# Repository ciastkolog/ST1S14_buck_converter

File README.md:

# ST1S14_buck_converter
ST1S14 buck converter board and documentation

Simple small step-down converter ST1S14:

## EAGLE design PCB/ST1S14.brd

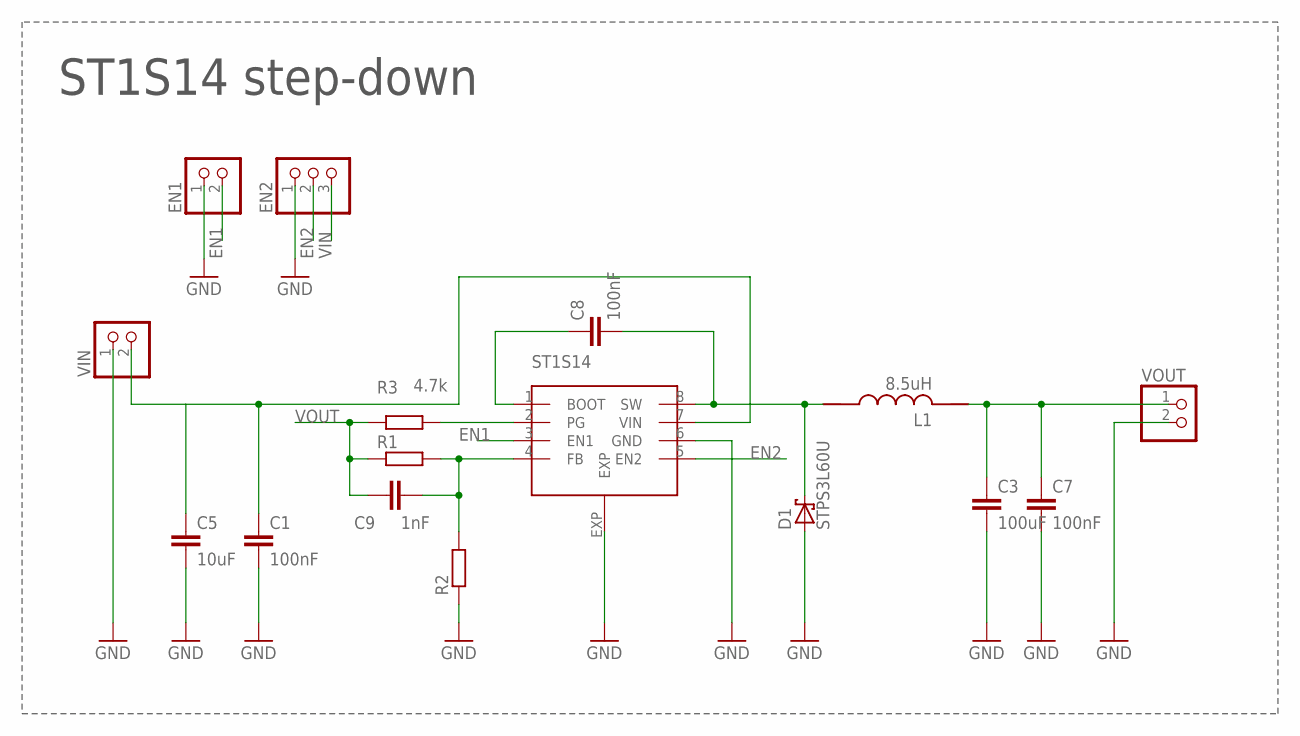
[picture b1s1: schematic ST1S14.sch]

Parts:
C1: 100nF; C1210K
C3: 100uF; C1210K
C5: 10uF; C0603
C7, C8: 100nF; C0603
C9: 1nF; C0603
D1: STPS3L60U; SMB
EN1: PINHD-1X2; 1X02
EN2: PINHD-1X3; 1X03
L1: 8.5uH; COIL1
R1, R2: R-EU_R0603; R0603
R3: 4.7k; R0603
U$1: ST1S14; HSOP8
VIN: PINHD-1X2; 1X02
VOUT: PINHD-1X2; 1X02

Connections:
EN1: EN1.2, U$1.3 (EN1)
EN2: EN2.2, U$1.5 (EN2)
GND: C1.2, C3.2, C5.2, C7.2, D1.A, EN1.1, EN2.1, R2.1, U$1.6 (GND), U$1.EXP, VIN.1, VOUT.2
unnamed: C8.1, U$1.1 (BOOT)
unnamed: C9.2, R1.2, R2.2, U$1.4 (FB)
unnamed: C8.2, D1.C, L1.1, U$1.8 (SW)
unnamed: R3.2, U$1.2 (PG)
VIN: C1.1, C5.1, EN2.3, U$1.7 (VIN), VIN.2
VOUT: C3.1, C7.1, C9.1, L1.2, R1.1, R3.1, VOUT.1

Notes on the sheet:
ST1S14 step-down

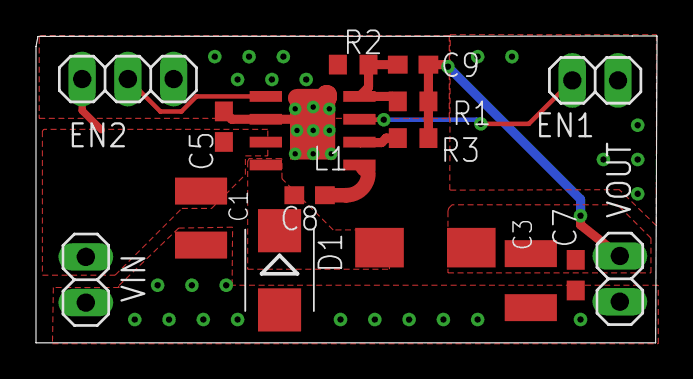
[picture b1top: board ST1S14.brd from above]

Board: 2 copper layers, 34.5 x 17.0 mm, 16 parts (0 on the bottom side), 9 nets.

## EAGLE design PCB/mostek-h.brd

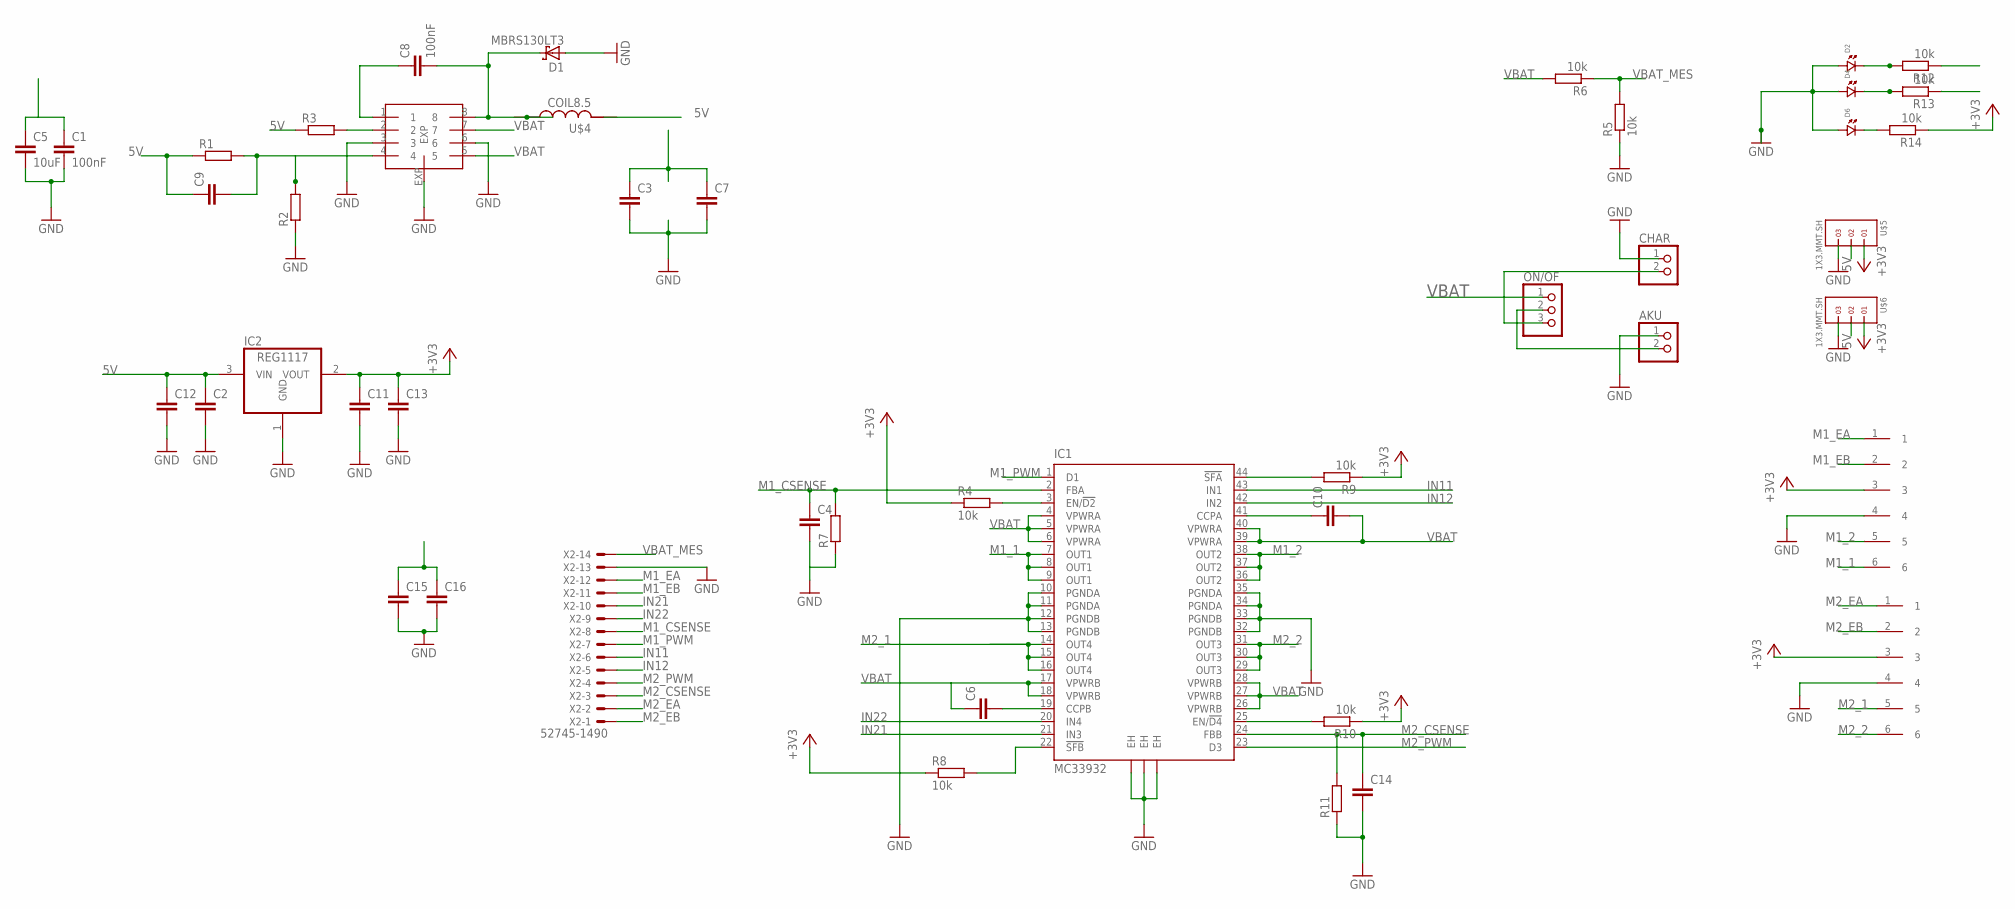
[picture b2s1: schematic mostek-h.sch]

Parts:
AKU: PINHD-1X2/90; 1X02/90
C1: 100nF; C1210K
C2, C6, C10, C11: C-EUC0805; C0805
C3, C15: C-EUC1210K; C1210K
C4, C7, C9, C14, C16: C-EUC0603; C0603
C5: 10uF; C0603
C8: 100nF; C0603
C12, C13: C-EUC1210; C1210
CHAR: PINHD-1X2/90; 1X02/90
D1: MBRS130LT3; SMB
D2, D4, D6: LED.0805; 0805.LED
IC1: MC33932; HSOP44
IC2: REG1117; SOT223
ON/OF: PINHD-1X3/90; 1X03/90
R1, R2, R3, R7, R11: R-EU_R0603; R0603
R4, R5, R6, R8, R9, R10, R12, R13, R14: 10k; R0603
U$1, U$2: PAD_SMD_6X1; SMD_6X1
U$3: ST1S14; HSOP8
U$4: COIL8.5; COIL1
U$5, U$6: 1X3.MMT.SH; 1X3_MMT.103.01.X.SH
X2: 52745-1490

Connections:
5V: C2.1, C3.1, C7.1, C9.1, C12.1, IC2.3 (VIN), R1.1, R3.1, R13.1, U$4.2, U$5.2, U$6.2
+3V3: C11.1, C13.1, IC2.2 (VOUT), R4.1, R8.1, R9.1, R10.1, R14.1, U$1.3, U$2.3, U$5.1, U$6.1
GND: AKU.1, C1.2, C2.2, C3.2, C4.2, C5.2, C7.2, C11.2, C12.2, C13.2, C14.2, C15.2, C16.2, CHAR.1, D1.A, D2.P$1 (1), D4.P$1 (1), D6.P$1 (1), IC1.10 (PGNDA), IC1.11 (PGNDA), IC1.12 (PGNDB), IC1.13 (PGNDB), IC1.32 (PGNDB), IC1.33 (PGNDB), IC1.34 (PGNDA), IC1.35 (PGNDA), IC1.EH@1 (EH), IC1.EH@2 (EH), IC1.EH@3 (EH), IC2.1 (GND), R2.1, R5.1, R7.1, R11.1, U$1.4, U$2.4, U$3.3, U$3.6, U$3.EXP, U$5.3, U$6.3, X2.13
IN11: IC1.43 (IN1), X2.6
IN12: IC1.42 (IN2), X2.5
IN21: IC1.21 (IN3), X2.10
IN22: IC1.20 (IN4), X2.9
M1_1: IC1.7 (OUT1), IC1.8 (OUT1), IC1.9 (OUT1), U$1.6
M1_2: IC1.36 (OUT2), IC1.37 (OUT2), IC1.38 (OUT2), U$1.5
M1_CSENSE: C4.1, IC1.2 (FBA), R7.2, X2.8
M1_EA: U$1.1, X2.12
M1_EB: U$1.2, X2.11
M1_PWM: IC1.1 (D1), X2.7
M2_1: IC1.14 (OUT4), IC1.15 (OUT4), IC1.16 (OUT4), U$2.5
M2_2: IC1.29 (OUT3), IC1.30 (OUT3), IC1.31 (OUT3), U$2.6
M2_CSENSE: C14.1, IC1.24 (FBB), R11.2, X2.3
M2_EA: U$2.1, X2.2
M2_EB: U$2.2, X2.1
M2_PWM: IC1.23 (D3), X2.4
unnamed: AKU.2, ON/OF.2
unnamed: CHAR.2, ON/OF.3
unnamed: C10.1, IC1.41 (CCPA)
unnamed: C8.1, U$3.1
unnamed: C8.2, D1.C, U$3.8, U$4.1
unnamed: R3.2, U$3.2
unnamed: C9.2, R1.2, R2.2, U$3.4
unnamed: IC1.3 (EN/!D2), R4.2
unnamed: C6.2, IC1.19 (CCPB)
unnamed: IC1.22 (!SFB), R8.2
unnamed: IC1.25 (EN/!D4), R10.2
unnamed: IC1.44 (!SFA), R9.2
unnamed: D2.P$2 (2), R12.2
unnamed: D4.P$2 (2), R13.2
unnamed: D6.P$2 (2), R14.2
VBAT: C1.1, C5.1, C6.1, C10.2, C15.1, C16.1, IC1.4 (VPWRA), IC1.5 (VPWRA), IC1.6 (VPWRA), IC1.17 (VPWRB), IC1.18 (VPWRB), IC1.26 (VPWRB), IC1.27 (VPWRB), IC1.28 (VPWRB), IC1.39 (VPWRA), IC1.40 (VPWRA), ON/OF.1, R6.2, R12.1, U$3.5, U$3.7
VBAT_MES: R5.2, R6.1, X2.14

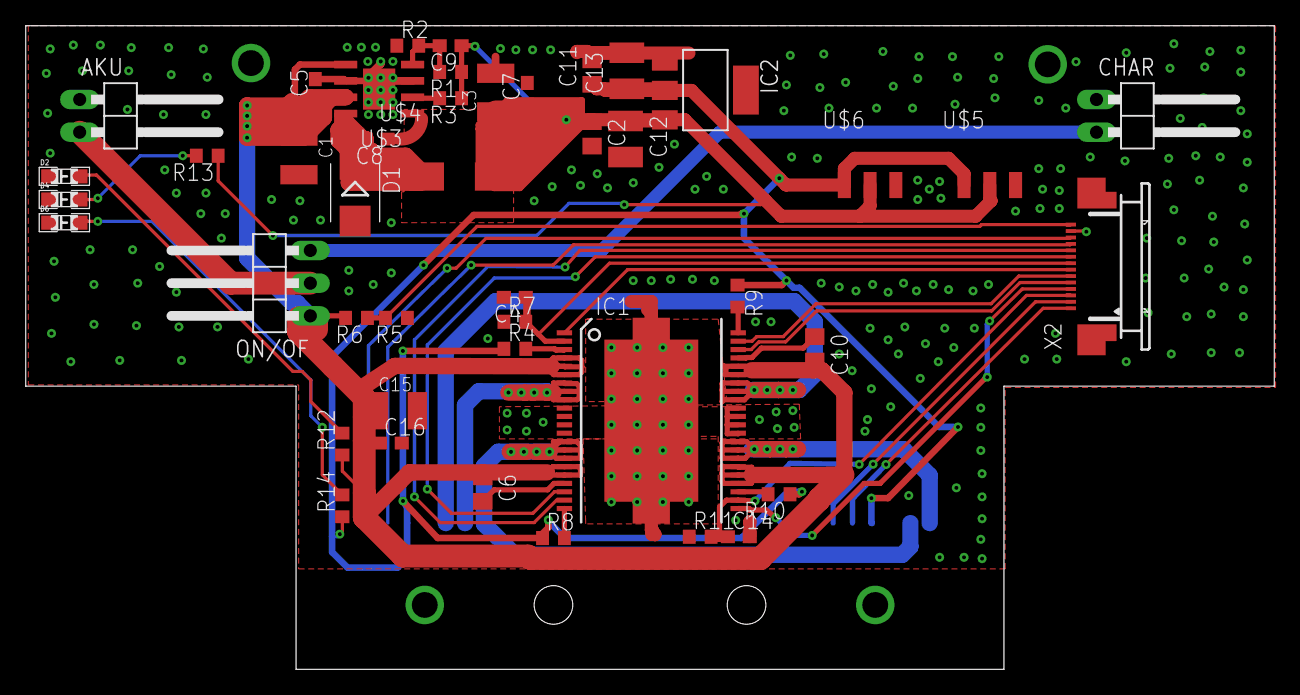
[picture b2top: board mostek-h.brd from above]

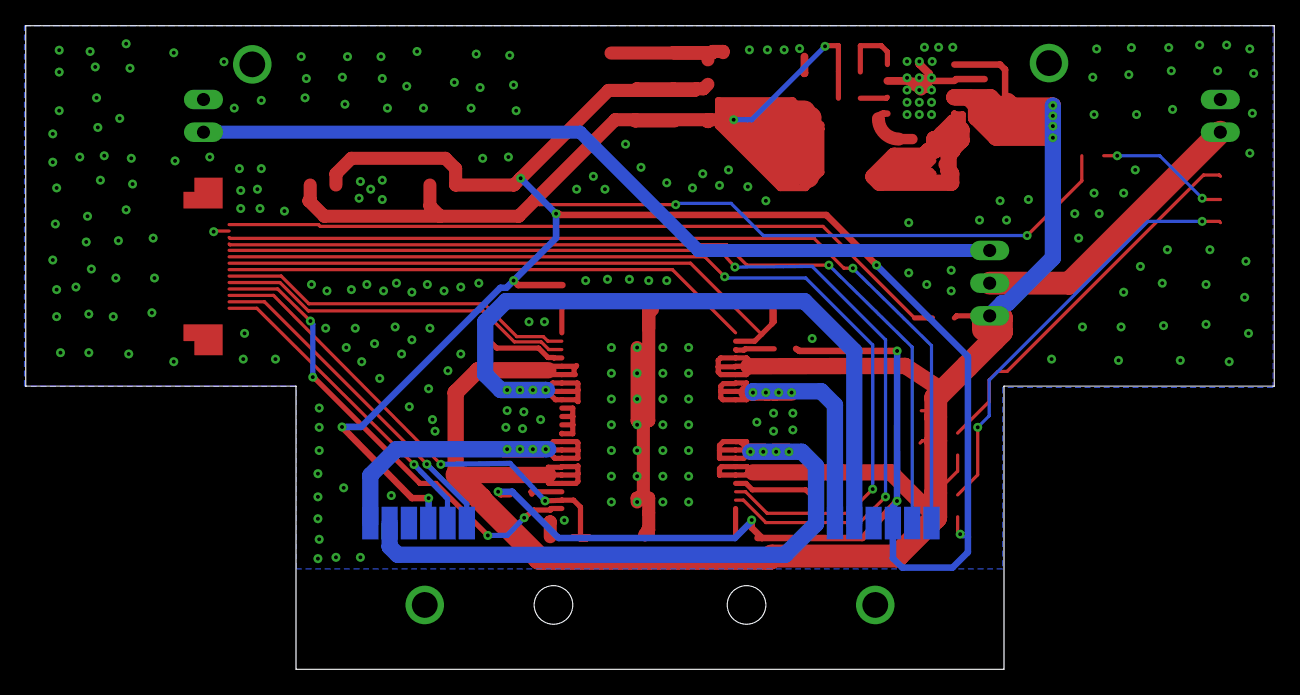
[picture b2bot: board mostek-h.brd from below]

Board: 2 copper layers, 97.0 x 50.0 mm, 46 parts (2 on the bottom side), 36 nets.

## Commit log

2018-03-07 Add documentation
2018-03-07 Ready schema
2018-03-07 Change file name
2018-03-07 Some changes on PCB
2018-03-07 Add net name VIN
2018-03-08 Ready board
2018-03-08 Add schema and board comp image
